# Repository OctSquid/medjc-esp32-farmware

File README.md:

# MEDJC09-HUB

## 概要

乾式筋電センサ`MEDJC-09`を最大 3 台まで制御できるハブデバイス</br>
センサの電圧読み取りは`MCP3208`を使用する．

## ハードウェア構成

[回路図](./docs/pcb.md)

- マイコン : ESP32
- ADC : `MCP3208`
- 筋電センサ : `MEDJC-09` 最大 3 台

### ADC チャネル対応

| チャネル番号 |     説明      |
| :----------: | :-----------: |
|     `0`      | MED`0`のME値  |
|     `1`      | MED`0`のSME値 |
|     `2`      | MED`1`のME値  |
|     `3`      | MED`1`のSME値 |
|     `4`      | MED`2`のME値  |
|     `5`      | MED`2`のSME値 |
|     `6`      |  ベース電圧   |

## コマンドフォーマット

ホストから UART で特定のコマンドを定められたバイナリフォーマットで送信する．</br>
バイナリの送信受信には[PacketSerial](https://github.com/bakercp/PacketSerial/tree/master)が使用される．</br>
送受信されるパケットは`COBS`エンコードされる．以下のフォーマットはデコード後のバイナリフォーマットである．

### 送信コマンド(HOST -> ESP32)

```bash
<コマンド> <ID> <パラメータ(オプション)>
[CMD] [ID] [PRM]
```

- `コマンド` : コマンド一覧のコマンドを送信する．コマンド一覧を参照．
- `ID` : コマンド送受信を対応させるための識別子. 16bit符号なし整数.
- `パラメータ` : コマンドによって送信するパラメータのサイズは異なる．

### 応答コマンド(ESP32 -> HOST)

コマンドが正常に処理された場合，ACK 応答を経た後，応答コマンドを返す．</br>

```bash
<応答コマンド> <ID> <パラメータ(オプション)>
[CMD] [ID] [PRM]
```

- `応答コマンド` : コマンド一覧の応答コマンドを返す．
- `ID` : コマンド送受信を対応させるための識別子. 16bit符号なし整数.
- `パラメータ` : コマンドによって返すパラメータのサイズは異なる．

> [!NOTE]
> すべてのコマンドはCOBSエンコードされて送受信されます。

### ERR 応答(ESP32 -> HOST)

コマンドが正常に処理されなかった場合，エラーコマンドを返す．</br>
特定のコマンドに対応するエラーコードがある．

```bash
# 0xFE <ERRコード> 0xFD
[SER] [ERRCode] [EER]
```

- `SERTX` : エラー応答の開始を示す．エラー応答の開始には必ず SERTX`0xFE`を返す．
- `ERRコード` : エラーコードを返す．ERR コード一覧を参照．
- `EERTX` : エラー応答の終了を示す．エラー応答の終了には必ず EERTX`0xFD`を返す．

#### ERR コード一覧(共通)

| ERR コード |               エラー内容               |
| :--------: | :------------------------------------: |
|   `0x01`   |            コマンド構文不正            |
|   `0x11`   |   コマンド無効(対応するコマンドなし)   |
|   `0x21`   | パラメータ無効(対応するパラメータなし) |

### コマンド一覧

- ファームウェアバージョンの取得
- ベース電圧の取得
- センサの接続状態の確認
- センサの ME 読み取り
- センサの SME 読み取り

| コマンド | コマンド名 |          コマンド説明          |
| :------: | :--------: | :----------------------------: |
|  `0x00`  |   `PING`   |       デバイスの生存確認       |
|  `0x01`  |  `GETVER`  | ファームウェアバージョンの取得 |
|  `0x02`  |  `GETBV`   |        ベース電圧の取得        |
|  `0x20`  |  `GETCON`  |     センサの接続状態の確認     |
|  `0x30`  |  `GETME`   |      センサの ME 読み取り      |
|  `0x31`  |  `GETSME`  |     センサの SME 読み取り      |
|  `0x40`  |  `STAPRM`  | ポーリングレポートモードの開始 |
|  `0x41`  |  `ENDPRM`  | ポーリングレポートモードの終了 |
|  `0x42`  |  `SETPRR`  | ポーリングレポートレートの設定 |
|  `0x43`  |  `GETPRR`  | ポーリングレポートレートの取得 |
|  `0x4F`  |  `GETPR`   |    ポーリングレポートの取得    |

#### デバイスの生存確認

デバイスの生存確認を行う．

- 送信コマンド

```bash
0x00 [ID]
```

- 応答コマンド

```bash
0x00 [ID]
```

#### ファームウェアバージョンの取得

デバイスのファームウェアバージョンを取得する．

- 送信コマンド

```bash
0x01 [ID]
```

- 応答コマンド

```bash
0x01 [ID] [MJV] [MIV] [PTV]
# EX) 0x01 0x0000 0x01 0x00 0x00 -> v1.0.0
```

| パラメータ | サイズ  |        説明        |
| :--------: | :-----: | :----------------: |
|   `MJV`    | `1byte` | メジャーバージョン |
|   `MIV`    | `1byte` | マイナーバージョン |
|   `PTV`    | `1byte` |  パッチバージョン  |

#### ベース電圧の取得

デバイスのベース電圧を取得する．

- 送信コマンド

```bash
0x02 [ID]
```

- 応答コマンド

```bash
0x02 [ID] [VB]
# EX) 0x02 0x0000 0xFFFF -> 3.3V
```

| パラメータ | サイズ  |                                  説明                                   |
| :--------: | :-----: | :---------------------------------------------------------------------: |
|    `VB`    | `2byte` | ベース電圧.符号あり 16bit 整数.`0-3.3`V を`0-4095`の範囲に置き換えた値. |

- ベース電圧について

コマンドで得られた値を$`v_B`$とすると，ベース電圧$`V_B`$は次のように表される．

$$
\begin{align}
V_B = \frac{3.3}{4095} \times v
\end{align}
$$

#### センサの接続状態の確認

> [!CAUTION]
> v1.2.0 以降では MCP3208 を使用するため，このコマンドは機能しない．

デバイスに接続されているセンサの接続状態を確認する．

- 送信コマンド

```bash
0x20 [ID]
```

- 応答コマンド

```bash
0x20 [ID] [CON0] [CON1] [CON2] [CON3]
# EX) 0x20 0x0000 0x01 0x00 0x00 0x00 -> センサ0: 接続, センサ1: 未接続, センサ2: 未接続, センサ3: 未接続
```

|      パラメータ      | サイズ  |                             説明                              |
| :------------------: | :-----: | :-----------------------------------------------------------: |
| `CON{n}` (`n`:`0-3`) | `1byte` | センサの接続状態(`0x00`: `disconnected`, `0x01`: `connected`) |

#### センサの ME 読み取り

デバイスに接続されているセンサの ME 値を読み取る．

- 送信コマンド

```bash
0x30 [ID]
```

- 応答コマンド

```bash
0x30 [ID] [ME0] [ME1] [ME2] [ME3]
# EX) 0x30 0x0000 0x03 0xE8 0x03 0xE9 0x00 0x00 0x00 0x00 -> ME0: 1000, ME1: 1001, ME2: 0, ME3: 0
```

|     パラメータ     | サイズ  |                                      説明                                      |
| :----------------: | :-----: | :----------------------------------------------------------------------------: |
| `ME{n}`(`n`:`0-3`) | `2byte` | ME 値. 符号あり 16bit 整数の上位 bit・下位 bit.センサが接続されていない場合`0` |

- ME 値について

筋電信号 ME を $`E`$ とすると

$$
\begin{align}
- 2048 \leq E \leq  2047\\
\end{align}
$$

ベース電圧(V)を $`V_B`$ すると，筋電信号電圧 $`V_{E}`$ は次のように表される．

$$
\begin{align}

V_{E} = \begin{cases}
            \frac{E}{2047} \times V_B & (E \geq 0) \\
            \frac{E}{2048} \times V_B & (E < 0) \\
        \end{cases}
\\

- \frac{1}{2} V_B \leq V_{E} \leq \frac{1}{2} V_B \\

\end{align}
$$

#### センサの SME 読み取り

デバイスに接続されているセンサの SME 値を読み取る．

- 送信コマンド

```bash
0x31 [ID]
```

- 応答コマンド

```bash
0x31 [ID] [SME0] [SME1] [SME2] [SME3]
# EX) 0x31 0x0000 0x07 0xD0 0x07 0xD1 0x00 0x00 0x00 0x00 -> SME0: 2000, SME1: 2001, SME2: 0, SME3: 0
```

|     パラメータ      | サイズ  |                                      説明                                      |
| :-----------------: | :-----: | :----------------------------------------------------------------------------: |
| `SME{n}`(`n`:`0-3`) | `2byte` | SME 値.符号あり 16bit 整数の上位 bit・下位 bit.センサが接続されていない場合`0` |

- SME 値について

整流・平滑筋電信号 SME を $`E'`$ とすると

$$
\begin{align}
0 \leq E' \leq 4095 \\
\end{align}
$$

ベース電圧(V)を $`V_B`$ すると，整流・平滑筋電信号電圧 $`V_{E'}$ は次のように表される．

$$
\begin{align}
V_{E'} = \frac{E'}{4095} \times V_B \\
0 \leq V_{E'} \leq V_B \\
\end{align}
$$

#### ポーリングレポートモードの開始

デバイスの情報一定間隔で自動的に送信するモードの開始．
[ポーリングレポートの取得](#ポーリングレポートの取得)で得られる応答コマンドを設定されたレートで送信する．
なお，ポーリングレポートモードで送信されたレポートのIDは`0`となる．

- 送信コマンド

```bash
0x40 [ID]
```

- 応答コマンド

```bash
0x40 [ID]
```

#### ポーリングレポートモードの終了

デバイスのポーリングレポートモードを終了する．

- 送信コマンド

```bash
0x41 [ID]
```

- 応答コマンド

```bash
0x41 [ID]
```

#### ポーリングレポートレートの設定

デバイスのポーリングレポートレートをHzで設定する．

- 送信コマンド

```bash
0x42 [ID] [RATE]
# EX) 0x42 0x0000 0x00 0x64 -> 100hz
```

| パラメータ | サイズ  |                                       説明                                       |
| :--------: | :-----: | :------------------------------------------------------------------------------: |
|   `RATE`   | `2byte` | ポーリングレポートレート.符号あり 16bit 整数の上位 bit・下位 bit. Hzで設定する． |

- 応答コマンド

```bash
0x42 [ID]
```

#### ポーリングレポートレートの取得

デバイスのポーリングレポートレートを取得する．

- 送信コマンド

```bash
0x43 [ID]
```

- 応答コマンド

```bash
0x43 [ID] [RATE]
# EX) 0x43 0x0000 0x00 0x64 -> 100Hz
```

| パラメータ | サイズ  |                                 説明                                  |
| :--------: | :-----: | :-------------------------------------------------------------------: |
|   `RATE`   | `2byte` | ポーリングレポートレート(Hz).符号あり 16bit 整数の上位 bit・下位 bit. |

#### ポーリングレポートの取得

デバイスのポーリングレポートを取得する．

- 送信コマンド

```bash
0x4F [ID]
```

- 応答コマンド

```bash
0x40 [ID] [VB] [ME0] [ME1] [ME2] [ME3] [SME0] [SME1] [SME2] [SME3] [TMP]
```

|     パラメータ      | サイズ  |                                                   説明                                                    |
| :-----------------: | :-----: | :-------------------------------------------------------------------------------------------------------: |
|        `VB`         | `2byte` |                   ベース電圧.符号あり 16bit 整数.`0-5`V を`0-4095`の範囲に置き換えた値.                   |
| `ME{n}`(`n`:`0-3`)  | `2byte` |              ME 値. 符号あり 16bit 整数の上位 bit・下位 bit.センサが接続されていない場合`0`               |
| `SME{n}`(`n`:`0-3`) | `2byte` |              SME 値.符号あり 16bit 整数の上位 bit・下位 bit.センサが接続されていない場合`0`               |
|        `TMP`        | `4byte` | レポート送信時のタイムスタンプ. ESP32 が起動してからの時間(ms). 符号なし 32bit 整数を 4 分割した byte 列. |

各パラメータの詳細は該当するコマンドの説明を参照．

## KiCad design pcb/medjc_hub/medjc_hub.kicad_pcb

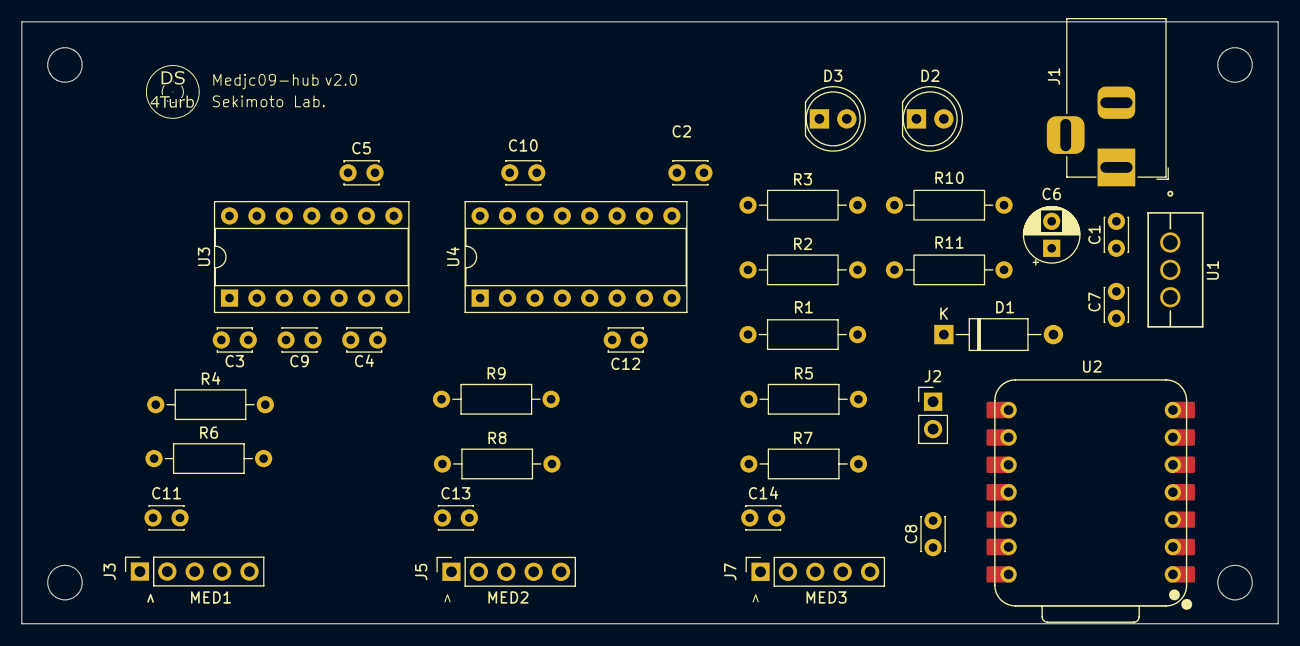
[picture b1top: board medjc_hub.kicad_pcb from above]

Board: 2 copper layers, 116.5 x 55.8 mm, 41 parts (0 on the bottom side), 27 nets, no tracks yet.

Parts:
C1, C2, C3, C4, C5, C7, C8, C9, C10, C11, C12, C13, C14: 0.1μF; C_Disc_D3.0mm_W2.0mm_P2.50mm
C6: 47μF; CP_Radial_D5.0mm_P2.50mm
D1: 1N4007; D_A-405_P10.16mm_Horizontal
D2, D3: LED; LED_D5.0mm
J1: MJ-180P; BarrelJack_Horizontal
J2: Conn_01x02_Pin; PinHeader_1x02_P2.54mm_Vertical
J3, J5, J7: Conn_01x05_Socket; PinSocket_1x05_P2.54mm_Vertical
R1, R2, R4, R5, R6, R7, R8, R9: 10kΩ; R_Axial_DIN0207_L6.3mm_D2.5mm_P10.16mm_Horizontal
R3: 5kΩ; R_Axial_DIN0207_L6.3mm_D2.5mm_P10.16mm_Horizontal
R10, R11: 200Ω; R_Axial_DIN0207_L6.3mm_D2.5mm_P10.16mm_Horizontal
REF1, REF2, REF3, REF4: MountingHole_3.2mm_M3
U1: BA033CC0T
U2: XIAO-ESP32-S3-DIP; XIAO-ESP32S3-DIP
U3: NJM2747D; DIP-14_W7.62mm_Socket
U4: MCP3208-CI_P; DIP-16_W7.62mm_Socket

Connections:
+3V3: C9.1, C10.1, C11.1, C12.1, C13.1, C14.1, D1.1 (K), J2.2, J3.1, J5.1, J7.1, R1.1, U3.4 (+Vin), U4.7 (CH6), U4.15 (VREF), U4.16 (VDD)
FME1: R4.2, U3.1 (OUT_A), U4.1 (CH0)
FME2: R9.2, U3.7 (OUT_B), U4.3 (CH2)
FME3: R5.1, U3.8 (OUT_C), U4.5 (CH4)
GND: C1.2, C2.2, C3.2, C4.2, C5.2, C6.2, C7.1, C8.2, C9.2, C10.2, C11.2, C12.2, C13.2, C14.2, D2.1 (K), D3.1 (K), J1.2, J3.3, J5.3, J7.3, R2.2, R3.2, U1.2 (N.C./GND), U2.13 (GND), U3.11 (GND), U4.9 (DGND), U4.14 (AGND)
IN_AMP_A: C2.1, C3.1, C4.1, C5.1, R1.2, R2.1, R3.1, U3.3 (+IN_A), U3.5 (+IN_B), U3.10 (+IN_C)
MISO: U2.10 (D9), U4.12 (DOUT)
MOSI: U2.11 (D10), U4.11 (DIN)
unnamed: C6.1, C7.2, D1.2 (A), U1.3 (OUT)
unnamed: D2.2 (A), R10.2
unnamed: D3.2 (A), R11.2
unnamed: C8.1, J2.1, U2.12 (VCC_3V3)
unnamed: J3.4, J5.4, J7.4
unnamed: C1.1, J1.1, U1.1 (Vcc)
unnamed: R4.1, R6.2, U3.2 (-IN_A)
unnamed: R8.2, R9.1, U3.6 (-IN_B)
unnamed: R5.2, R7.1, U3.9 (-IN_C)
POWER_LED: R10.1, U2.4 (D3)
RAWME1: J3.2, R6.1
RAWME2: J5.2, R8.1
RAWME3: J7.2, R7.2
SCK: U2.9 (D8), U4.13 (CLK)
SME1: J3.5, U4.2 (CH1)
SME2: J5.5, U4.4 (CH3)
SME3: J7.5, U4.6 (CH5)
SS: U2.6 (D5), U4.10 (~CS/SHDN)
STATUS_LED: R11.1, U2.5 (D4)

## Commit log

2024-05-26 🎉 Init: プロジェクト作成
2024-05-26 ✨ Add: 基本機能実装
2024-05-26 ✅ Add: テスト追加
2024-05-26 👷 Add: GithubActions Build 追加
2024-05-26 💚 Fix: extra_configsのセクションを修正
2024-05-26 🙈 Add: ports.ini
2024-05-26 🔥 Remove: ports.ini
2024-05-26 📝 Update: 応答コマンドバイナリの仕様変更に対応
2024-05-26 🔥 Remove: ACK応答を削除
2024-05-26 📝 Add: ポーリングレポートモードの仕様を追加
2024-05-26 ✨ Add: ポーリングレポートモードのコマンド追加
2024-05-26 ✅ ポーリングレポートモードのテスト追加
2024-05-26 🔧 Remove: 不要な設定の削除
2024-05-26 🔥 Remove: デバッグ用のコードの削除
2024-05-27 📝 Update: ポーリングレポートコマンドの仕様を変更
2024-05-27 ✨ Add: ポーリングレポート取得コマンドを追加
2024-05-27 ✅ Add: ポーリングレポート取得コマンドのテストを追加
2024-05-27 ⚡️ Improve: ads1115の読み取り速度の高速化
2024-05-27 ⚡️ Improve: 高速化
2024-05-27 ⚡️ Update: レポートの余分なデータを削除
2024-05-27 ✨ Add: レポートにタイムスタンプを追加
2024-05-27 ✅ Add: タイムスタンプのテストを追加
2024-05-27 ⚡️ Improve: マルチタスク化
2024-05-27 ⚡️ Improve: hwタイマーを使用するように変更
2024-05-27 ✅ Update: テストでupdate()を使用しないよう更新
2024-05-27 🐛 Fix: SMEの読み取りチャネルを修正
2024-05-29 ⚡️ Improve: I2Cのクロックスピードを向上
2024-05-29 📝 Update: レートの指定をHzで行うように変更
2024-05-29 💥 Update: ポーリングレートをHzで指定するように
2024-05-29 ✅ Test: ポーリングレートの仕様変更に対応
2024-05-29 ⚡️ Improve: マイクロ秒単位で実行できるように
2024-05-29 🔧 Add: ビルドオプションを追加
2024-05-29 ⚡️ Improve: sendReportにIRAM_ATTR修飾子を追加
2024-05-29 💥 Change: ADCをstatic化
2024-05-29 🚑 Fix: virtual つけ忘れ
2024-05-29 🤡 Mock: ADCのモック
2024-05-29 ✅ Test: ADCのstatic化に対応
2024-05-29 💥 Change: コマンドハンドラのstatic化
2024-05-29 🤡 Mock: コマンドハンドラ用Mock
2024-05-29 ✅ Test: コマンドハンドラのテストに対応
2024-05-29 ⚡️ Improve: packetの監視処理をcore1で実行
2024-05-30 🎨 Style: inline 修飾子の位置を調整
2024-05-30 ⚡️ Improve: ボーレートを 921600 bps に設定
2024-05-30 ⚡️ Improve: ポーリングの送信処理をupdate関数で行うように変更
2024-05-30 ✅ Test: テストのボートレートを 921600bps に設定
2024-05-30 📝 Doc: コメントを追加
2024-05-30 🎨 Change: バージョン番号をマクロに変更
2024-05-30 ✨ Update: バージョンインクリメント 1.1.0
2024-05-30 🔥 Remove: 不要なinclude削除
2024-05-30 🎨 Style: format
2024-05-31 🙈 Add: .DS_Store
2024-05-31 🚧 WIP: kicad回路図を追加
2024-06-03 🚧 WIP: Kicad 回路図を更新
2024-07-06 📝 Update: 回路図を更新
2024-07-14 💥 Update: MCP3208に適用
2024-07-14 🔧 Add: c3 super mini用の構成を追加
2024-07-14 ✨ Update: バージョンインクリメント 1.2.0
2024-07-14 📝 Update: ハード仕様を更新
2024-07-14 🐛 Fix: ME値とSME値の計算が逆になっていたのを修正
2024-07-14 📝 Update: MCP3208に適用
2024-07-16 ✨ add: pingコマンドを実装
2024-07-16 🐛 fix: pingコマンドのハンドラの追加し忘れ
2024-07-23 ➖ remove: 不要な依存関係の削除
2024-07-23 ✨ feat: ADCにreadAll系関数を追加
2024-07-23 ✨ feat: コマンドの送受信にIDが必要に
2024-07-23 🔥 remove: 不要なinclude文を削除
2024-07-23 📝 update: コマンド構文を更新(ID)
2024-07-23 ✅ test: テストを新コマンド構文に対応
2024-07-23 ✨ update: バージョン変更 1.4.0
2025-01-11 📝 Update: 部品情報を更新
2025-01-11 📝 Update: アクティブレイヤーを0に変更
2025-01-11 ✨ update: ボード設定をesp32-c3-devkitm-1に変更
2025-01-11 📝 add: テスト実行に関するメモを追加
2025-01-11 ✨ update: コマンドパーサーのバッファ処理を簡素化し、STX/ETXを削除
2025-01-11 🩹 fix: パラメータの開始位置の修正
2025-01-11 🔖 update: バージョン番号を1.4から1.5に更新
2025-01-12 📝 docs: READMEにポーリングレポートモードのIDについての説明を追加
2025-10-05 ✨ add: seeeduino_xiao環境をplatformio.iniに追加
2025-10-05 Update simulation waveform colors and add NJM2747D symbol library
    - Changed the waveform color for the input voltage (VIN) to a new RGB value.
    - Updated the waveform color for the output voltage (VOUT) to a different RGB value.
    - Added cursor formatting for both VIN and VOUT signals in the simulation.
    - Introduced a new symbol library for the NJM2747D component in the project.
2025-10-20 🍱 update: pcb v2
2025-10-20 🚑 fix: 末尾に空白を含んだパスを修正
